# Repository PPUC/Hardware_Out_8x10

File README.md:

# Lamp Matrix PCB for PPUC Project
This is the hardware for a LED lamp matrix card which was designed for the PPUC pinball project, but can be useful in other applications as well. The intentionally usecase is to connect an original equipped pinball playfield (including cable harness). Normally I'd prefer a serial WS2812 LED strip to do a DIY pinball but if all the LEDs and cables are in place already, it is useful to connect the lamp matrix directly (for LED use only, not for incandescent bulbs as power of the outputs is limited).
It is designed for being low cost and functional for experimental use.  
Not everything is tested nor does it fulfill EMC or any other specifications.  
Use at your own risk!
To make use of anything of this project a basic understanding of electronics and programming is necessary. Nothing of it is "plug and play". I'm surely not liable for any damage to assemblies, pinball machines or even persons.

## Picture of the Board

## Name
Out_8x10 as it has 18 outputs. 8 high side switches and 10 low side switches which can form a 8x10 matrix but could also be used as simple high side and low side outputs.  

## Power Supply
The IO card must be supplied by 5 V (+-0.5 V) for logic and nominal 20 V for outputs. As these outputs are open source and open drain, the 20 V supply can actually be 7 V up to 26 V. In the circuit diagram the voltage is called 20 V.

## Controller
A RP2040 is used for it's cost/performance ratio. It is the same controller that is used in the Raspberry Pi Pico.

## Communication Interfaces
* RS_485: main communication interface for controlling the outputs. Usually connected to a host interface like a PC or Raspberry Pi or similar.
* USB C: for programming, debug and flashing
* Serial Wire: alternative for programming, debug and flashing

## Switches (on board)
* Reset: hardware reset for controller (RP2040)
* Boot: if active, the board connects to a PC like an USB stick. Usually used for programming the code into the flash memory on the board.
* DIP-switches: usually used to select an address for RS485 (16 combinations)

## High Side Switch Outputs
There are 8 outputs featuring a high side switch, usually used for lamp coloums. The voltage is derived form 20 V power connection. Current and power is limited by a linear regulator (78L24) wich is actually not used for regulating the voltage but to protect the switch form overload in case of a short circuit. Each output can drive a constant current of 100 mA witch is normaly sufficiant for 10 LED lamps (e.g. 10 rows of LEDs). Short term peak current is about 300 mA. The 20 V supply can actually range from 7 V to 26 V (the lower limit is derived from UGS of the high side FET).

## Low Side Switch Outputs
There are 10 outputs featuring a low side switch, usually used for lamp rows. The outputs are open drain and drive currents up to 3 A with a load connected to a voltage of up to 30 V.

## Special Output
One special output is available for high speed signals. The voltage is 5 V, it is a push pull output that can drive a current up to 8 mA. It can be used to e.g. control a WS2812 LED strip.

## Connectors
There are pads for connectors that fit S.A.M. systems and also WPC systems. Be aware that J5 (WPC columns) is actually not in the PCB layout as it can be mounted on pins 1 to 9 of J6 (S.A.M. columns). The pinning is unfortunately vice versa so the connector of the original WPC cable harness has to be rotated by 180° (cables go to the inner side of PCB).

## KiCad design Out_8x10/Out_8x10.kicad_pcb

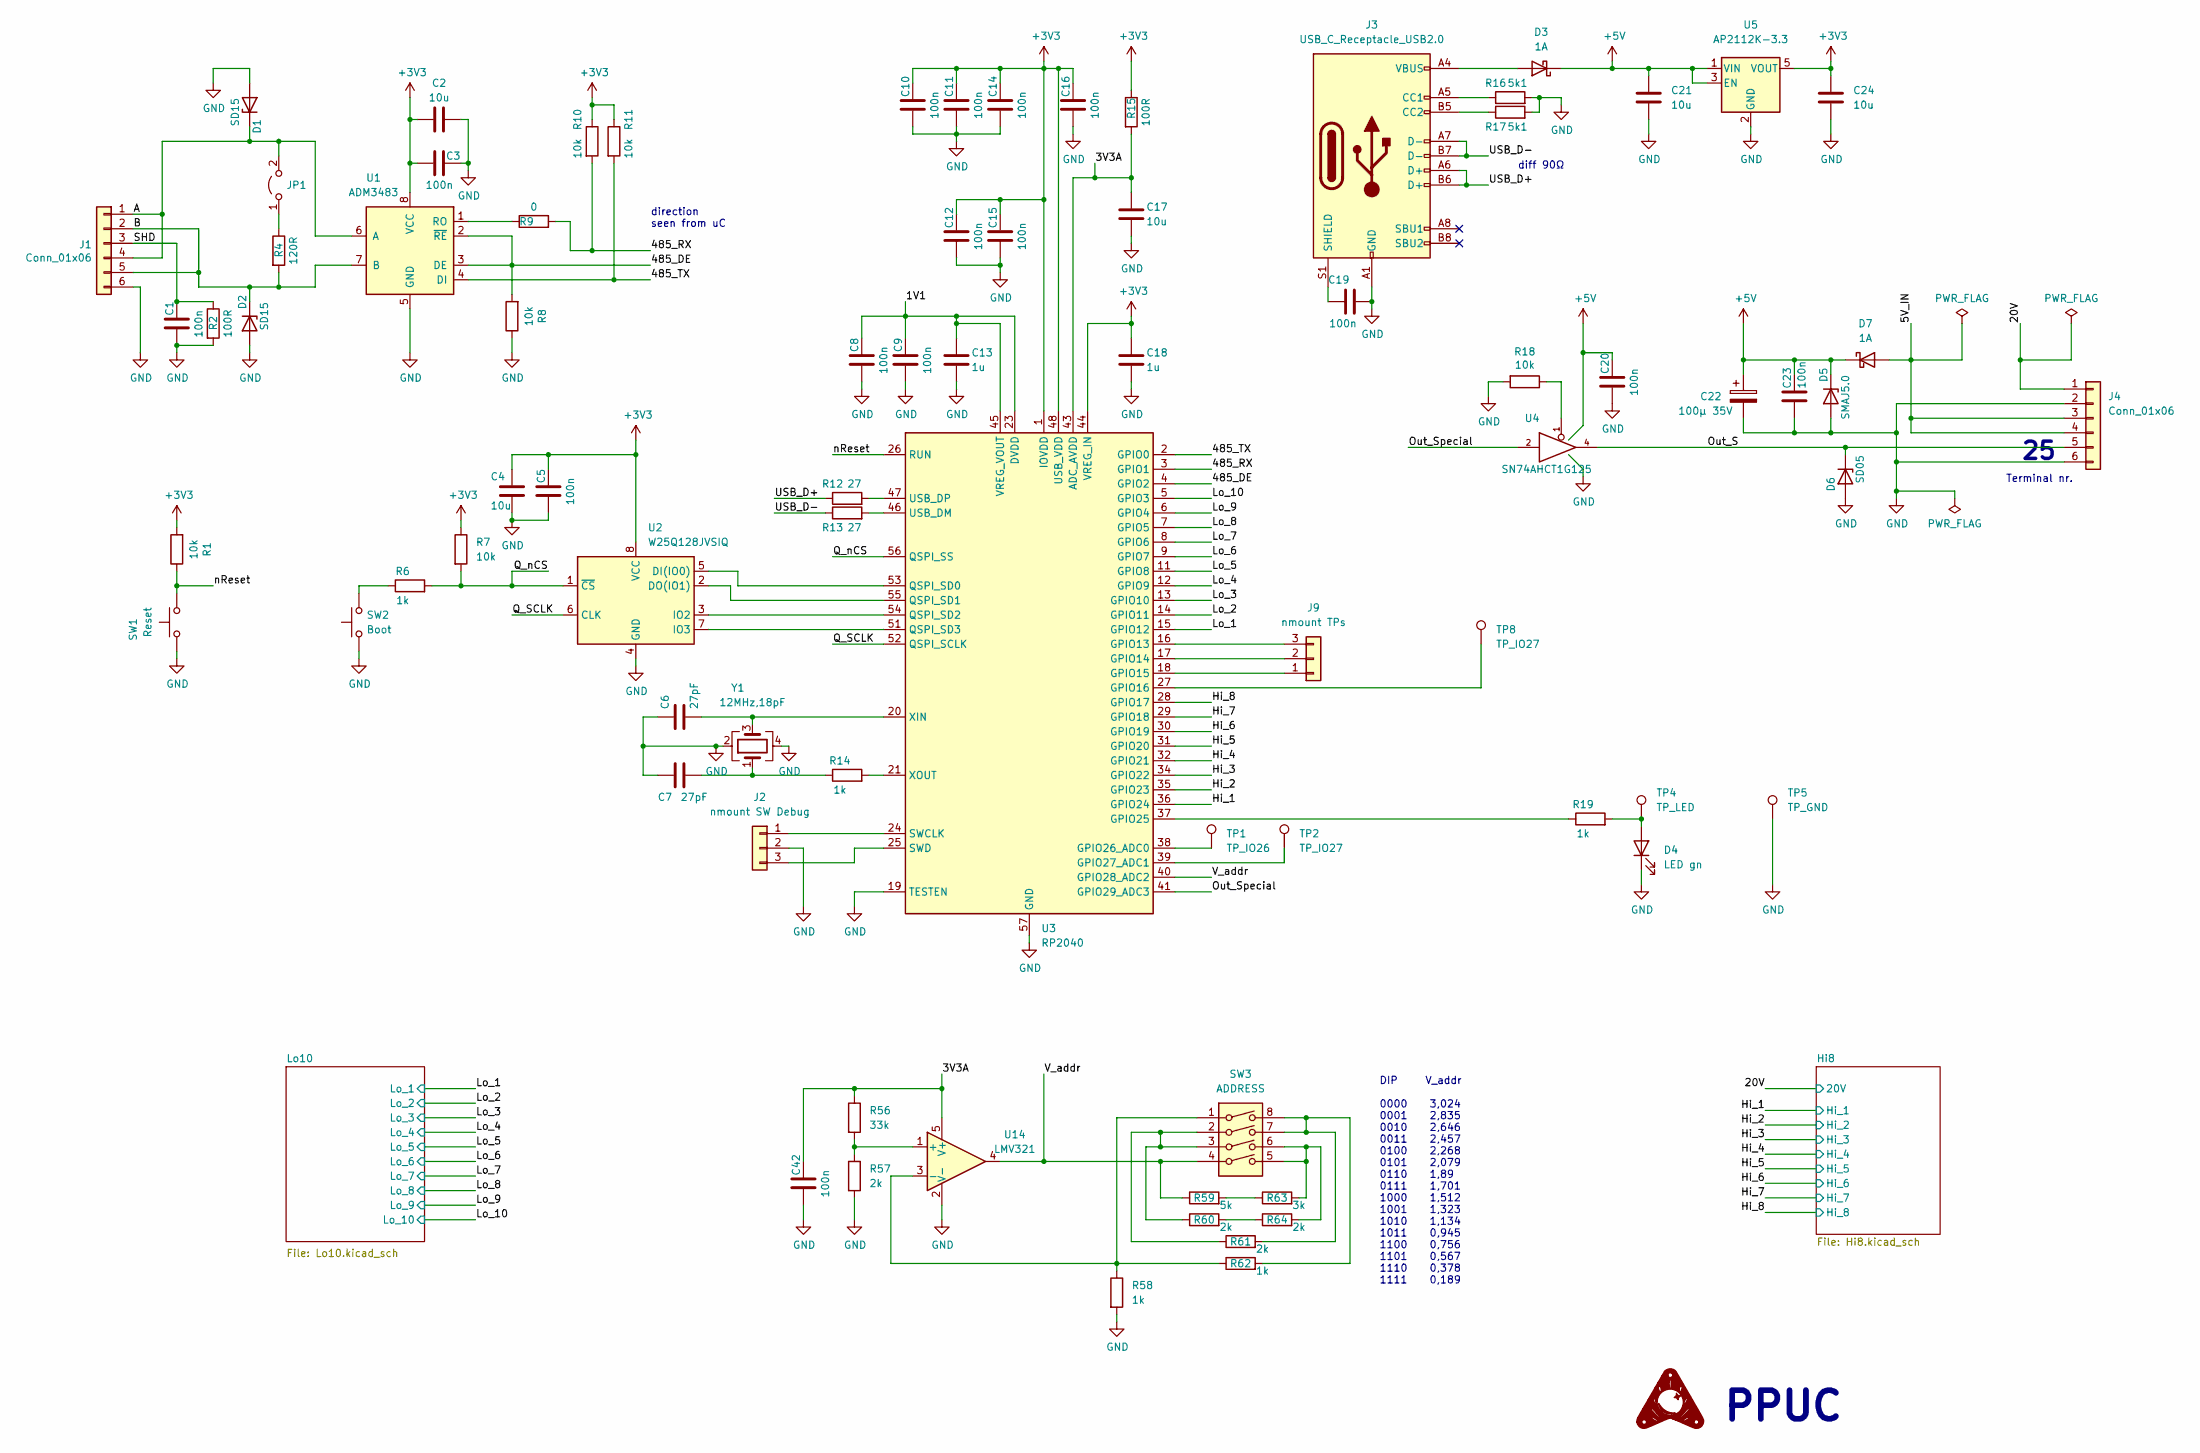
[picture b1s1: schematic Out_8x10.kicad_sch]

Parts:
C1, C3, C5, C8, C9, C10, C11, C12, C14, C15, C16, C19, C20, C23, C42: 100n; C_0402_1005Metric
C2, C4, C17, C21, C24: 10u; C_0603_1608Metric
C6, C7: 27pF; C_0402_1005Metric
C13, C18: 1u; C_0402_1005Metric
C22: 100µ 35V; CP_Elec_6.3x7.7; JLCPCB Rotation Offset 180
D1, D2: SD15; D_SOD-323
D3, D7: 1A; D_SOD-323
D4: LED gn; LED_0805_2012Metric
D5: SMAJ5.0; D_SMA
D6: SD05; D_SOD-323
J1, J4: Conn_01x06; Terminal_Block_RTMPin
J2: nmount SW Debug; PinSocket_1x03_P2.54mm_Vertical
J3: USB_C_Receptacle_USB2.0; USB_C_Receptacle_XKB_U262-16XN-4BVC11
J9: nmount TPs; PinSocket_1x03_P2.54mm_Vertical
JP1: Jumper_2_Open; PinHeader_1x02_P2.54mm_Vertical
R1, R7, R8, R10, R11, R18: 10k; R_0603_1608Metric
R2, R15: 100R; R_0603_1608Metric
R4: 120R; R_0603_1608Metric
R6, R14, R19, R58, R62: 1k; R_0402_1005Metric
R9: 0; R_0603_1608Metric
R12, R13: 27; R_0402_1005Metric
R16, R17: 5k1; R_0603_1608Metric
R56: 33k; R_0603_1608Metric
R57, R60, R61, R64: 2k; R_0603_1608Metric
R59: 5k; R_0603_1608Metric
R63: 3k; R_0603_1608Metric
SW1: Reset; SW_SPST_SKQG_WithStem
SW2: Boot; SW_SPST_SKQG_WithStem
SW3: ADDRESS; SW_DIP_SPSTx04_Slide_6.7x11.72mm_W8.61mm_P2.54mm_LowProfile; JLCPCB Rotation Offset 90
TP1: TP_IO26; TestPoint_Pad_D1.0mm
TP2, TP8: TP_IO27; TestPoint_Pad_D1.0mm
TP4: TP_LED; Pin_D1.0mm_L10.0mm
TP5: TP_GND; Pin_D1.0mm_L10.0mm
U1: ADM3483; SOIC-8_3.9x4.9mm_P1.27mm
U2: W25Q128JVSIQ; SOIC-8_5.23x5.23mm_P1.27mm
U3: RP2040; QFN-56-1EP_7x7mm_P0.4mm_EP3.2x3.2mm; JLCPCB Rotation Offset -90
U4: SN74AHCT1G125; SOT-23-5
U5: AP2112K-3.3; SOT-23-5; JLCPCB Rotation Offset 90
U14: LMV321; SOT-23-5
Y1: 12MHz,18pF; Crystal_SMD_3225-4Pin_3.2x2.5mm

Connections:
+3V3: C2.1, C3.1, C4.1, C5.1, C10.1, C11.1, C12.1, C14.1, C15.1, C16.1, C18.1, C24.1, R1.2, R7.1, R10.1, R11.1, R15.1, U1.8 (VCC), U2.8 (VCC), U3.1 (IOVDD), U3.10 (IOVDD), U3.22 (IOVDD), U3.33 (IOVDD), U3.42 (IOVDD), U3.44 (VREG_IN), U3.48 (USB_VDD), U3.49 (IOVDD), U5.5 (VOUT)
+5V: C20.1, C21.1, C22.1, C23.1, D3.1 (K), D5.1 (K), D7.1 (K), U4.5 (VCC), U5.1 (VIN), U5.3 (EN)
/1V1: C8.1, C9.1, C13.1, U3.23 (DVDD), U3.45 (VREG_VOUT), U3.50 (DVDD)
/3V3A: C17.1, C42.1, R15.2, R56.1, U3.43 (ADC_AVDD), U14.5 (V+)
/485_DE: R8.2, U1.2 (~RE), U1.3 (DE), U3.4 (GPIO2)
/485_RX: R9.2, R10.2, U3.3 (GPIO1)
/485_TX: R11.2, U1.4 (DI), U3.2 (GPIO0)
/A: D1.1 (K), J1.1, J1.4, JP1.2 (B), U1.6 (A)
/B: D2.1 (K), J1.2, J1.5, R4.2, U1.7 (B)
/Hi_1: U3.36 (GPIO24); also elsewhere on the board
/Hi_2: U3.35 (GPIO23); also elsewhere on the board
/Hi_3: U3.34 (GPIO22); also elsewhere on the board
/Hi_4: U3.32 (GPIO21); also elsewhere on the board
/Hi_5: U3.31 (GPIO20); also elsewhere on the board
/Hi_6: U3.30 (GPIO19); also elsewhere on the board
/Hi_7: U3.29 (GPIO18); also elsewhere on the board
/Hi_8: U3.28 (GPIO17); also elsewhere on the board
/Lo_1: U3.15 (GPIO12); also elsewhere on the board
/Lo_2: U3.14 (GPIO11); also elsewhere on the board
/Lo_3: U3.13 (GPIO10); also elsewhere on the board
/Lo_4: U3.12 (GPIO9); also elsewhere on the board
/Lo_5: U3.11 (GPIO8); also elsewhere on the board
/Lo_6: U3.9 (GPIO7); also elsewhere on the board
/Lo_7: U3.8 (GPIO6); also elsewhere on the board
/Lo_8: U3.7 (GPIO5); also elsewhere on the board
/Lo_9: U3.6 (GPIO4); also elsewhere on the board
/Lo_10: U3.5 (GPIO3); also elsewhere on the board
/Out_S: D6.1 (K), J4.5, U4.4
/Out_Special: U3.41 (GPIO29_ADC3), U4.2
/Q_SCLK: U2.6 (CLK), U3.52 (QSPI_SCLK)
/Q_nCS: R6.2, R7.2, U2.1 (~CS), U3.56 (QSPI_SS)
/SHD: C1.1, J1.3, R2.1
/USB_D+: J3.A6 (D+), J3.B6 (D+), R12.1
/USB_D-: J3.A7 (D-), J3.B7 (D-), R13.1
/V_addr: R59.1, SW3.4, U3.40 (GPIO28_ADC2), U14.4
/nReset: R1.1, SW1.2, U3.26 (RUN)
unnamed: C6.2, U3.20 (XIN), Y1.3
unnamed: C7.2, R14.1, Y1.1
unnamed: C19.1, J3.S1 (SHIELD)
unnamed: D3.2 (A), J3.A4 (VBUS), J3.A9 (VBUS), J3.B4 (VBUS), J3.B9 (VBUS)
unnamed: D4.2 (A), R19.2, TP4.1
unnamed: J2.1, U3.24 (SWCLK)
unnamed: J2.3, U3.25 (SWD)
unnamed: J3.A5 (CC1), R16.1
unnamed: J3.B5 (CC2), R17.1
unnamed: J9.1, U3.18 (GPIO15)
unnamed: J9.2, U3.17 (GPIO14)
unnamed: J9.3, U3.16 (GPIO13)
unnamed: JP1.1 (A), R4.1
unnamed: R6.1, SW2.2
unnamed: R9.1, U1.1 (RO)
unnamed: R12.2, U3.47 (USB_DP)
unnamed: R13.2, U3.46 (USB_DM)
unnamed: R14.2, U3.21 (XOUT)
unnamed: R18.1, U4.1
unnamed: R19.1, U3.37 (GPIO25)
unnamed: R56.2, R57.1, U14.1 (+)
unnamed: R58.1, R62.1, SW3.1, U14.3 (-)
unnamed: R59.2, R63.1
unnamed: R60.1, R61.1, SW3.2, SW3.3
unnamed: R60.2, R64.1
unnamed: R61.2, R62.2, SW3.7, SW3.8
unnamed: R63.2, R64.2, SW3.5, SW3.6
unnamed: TP1.1, U3.38 (GPIO26_ADC0)
unnamed: TP2.1, U3.39 (GPIO27_ADC1)
unnamed: TP8.1, U3.27 (GPIO16)
unnamed: U2.2 (DO(IO1)), U3.55 (QSPI_SD1)
unnamed: U2.3 (IO2), U3.54 (QSPI_SD2)
unnamed: U2.5 (DI(IO0)), U3.53 (QSPI_SD0)
unnamed: U2.7 (IO3), U3.51 (QSPI_SD3)

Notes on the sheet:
DIP V_addr 0000 3,024 0001 2,835 0010 2,646 0011 2,457 0100 2,268 0101 2,079 0110 1,89 0111 1,701 1000 1,512 1001 1,323 1010 1,134 1011 0,945 1100 0,756 1101 0,567 1110 0,378 1111 0,189
diff 90Ω
Terminal nr.
direction seen from uC
PPUC

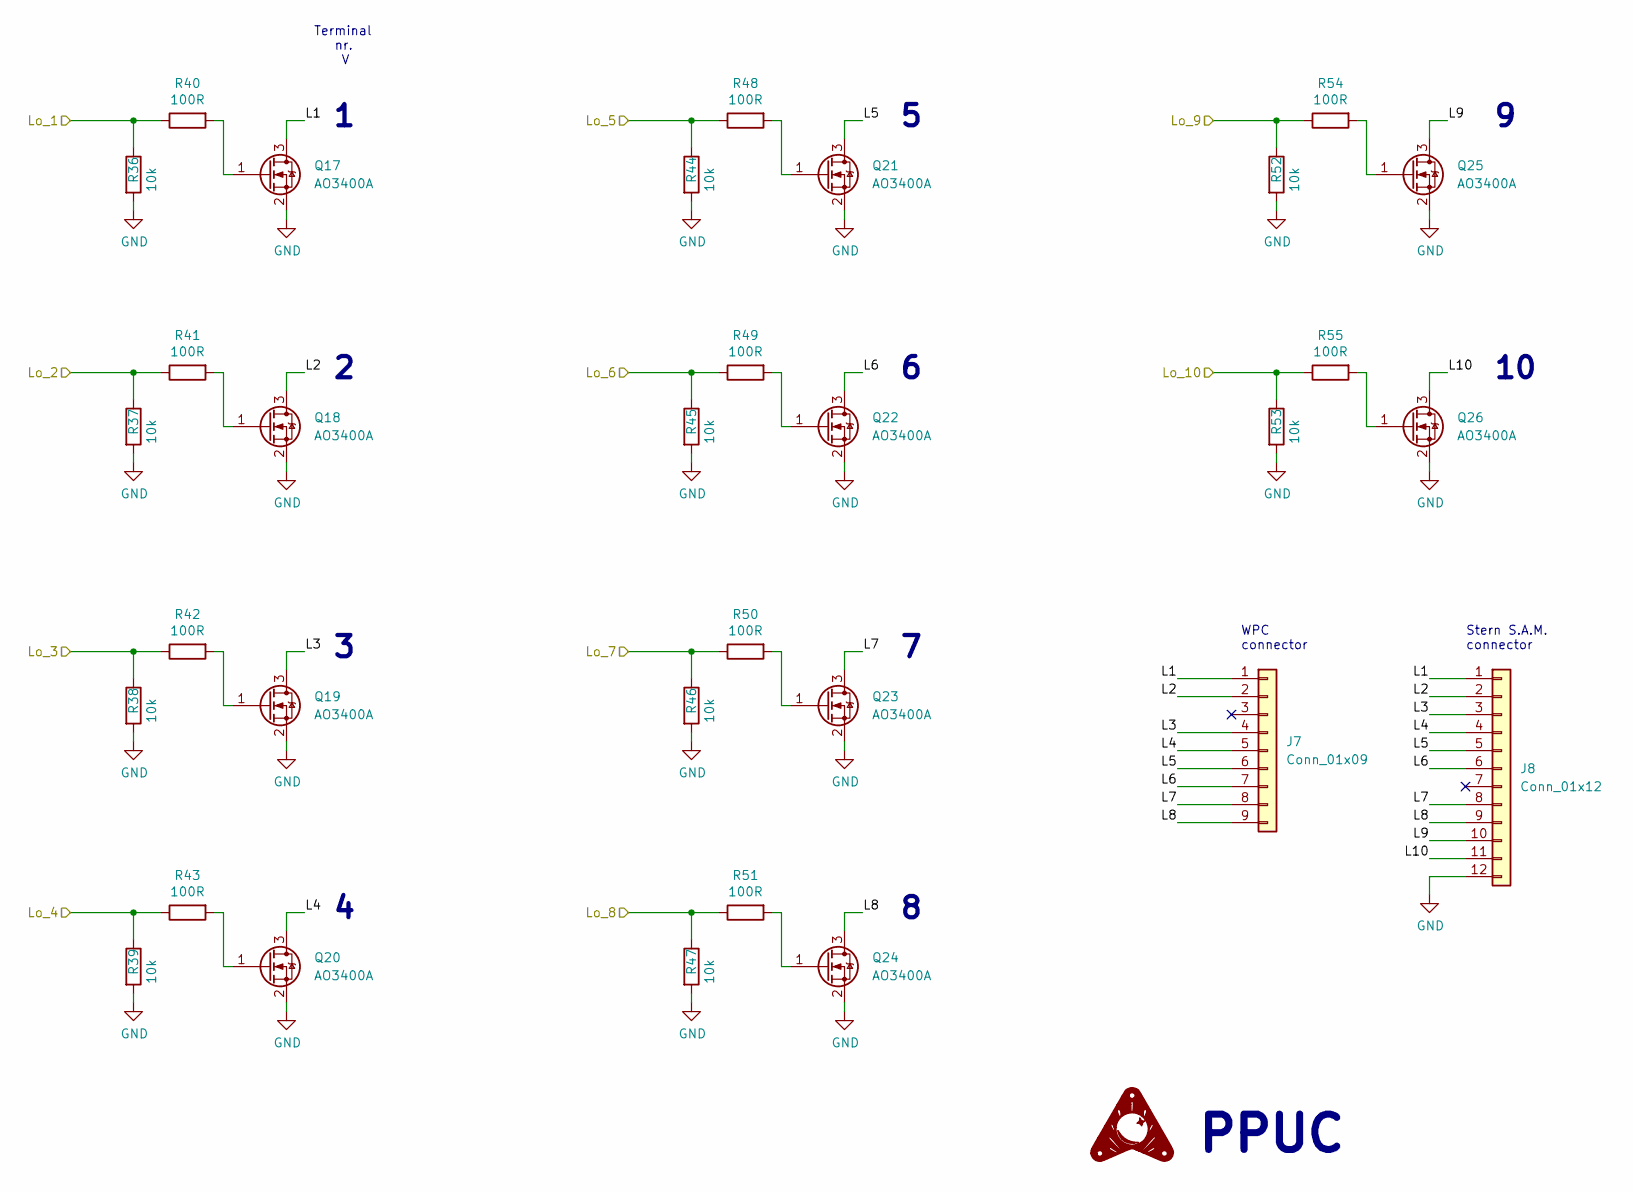
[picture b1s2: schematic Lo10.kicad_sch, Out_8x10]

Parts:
J7: Conn_01x09; Molex_KK-254_AE-6410-09A_1x09_P2.54mm_Vertical
J8: Conn_01x12; Molex_KK-396_5273-12A_1x12_P3.96mm_Vertical
Q17, Q18, Q19, Q20, Q21, Q22, Q23, Q24, Q25, Q26: AO3400A; SOT-23
R36, R37, R38, R39, R44, R45, R46, R47, R52, R53: 10k; R_0603_1608Metric
R40, R41, R42, R43, R48, R49, R50, R51, R54, R55: 100R; R_0603_1608Metric

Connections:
/Lo10/L1: J7.1, J8.1, Q17.3 (D)
/Lo10/L2: J7.2, J8.2, Q18.3 (D)
/Lo10/L3: J7.4, J8.3, Q19.3 (D)
/Lo10/L4: J7.5, J8.4, Q20.3 (D)
/Lo10/L5: J7.6, J8.5, Q21.3 (D)
/Lo10/L6: J7.7, J8.6, Q22.3 (D)
/Lo10/L7: J7.8, J8.8, Q23.3 (D)
/Lo10/L8: J7.9, J8.9, Q24.3 (D)
/Lo10/L9: J8.10, Q25.3 (D)
/Lo10/L10: J8.11, Q26.3 (D)
/Lo_1: R36.1, R40.1; also elsewhere on the board
/Lo_2: R37.1, R41.1; also elsewhere on the board
/Lo_3: R38.1, R42.1; also elsewhere on the board
/Lo_4: R39.1, R43.1; also elsewhere on the board
/Lo_5: R44.1, R48.1; also elsewhere on the board
/Lo_6: R45.1, R49.1; also elsewhere on the board
/Lo_7: R46.1, R50.1; also elsewhere on the board
/Lo_8: R47.1, R51.1; also elsewhere on the board
/Lo_9: R52.1, R54.1; also elsewhere on the board
/Lo_10: R53.1, R55.1; also elsewhere on the board
unnamed: Q17.1 (G), R40.2
unnamed: Q18.1 (G), R41.2
unnamed: Q19.1 (G), R42.2
unnamed: Q20.1 (G), R43.2
unnamed: Q21.1 (G), R48.2
unnamed: Q22.1 (G), R49.2
unnamed: Q23.1 (G), R50.2
unnamed: Q24.1 (G), R51.2
unnamed: Q25.1 (G), R54.2
unnamed: Q26.1 (G), R55.2

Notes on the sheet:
PPUC
WPC connector
Terminal nr. V
Stern S.A.M. connector

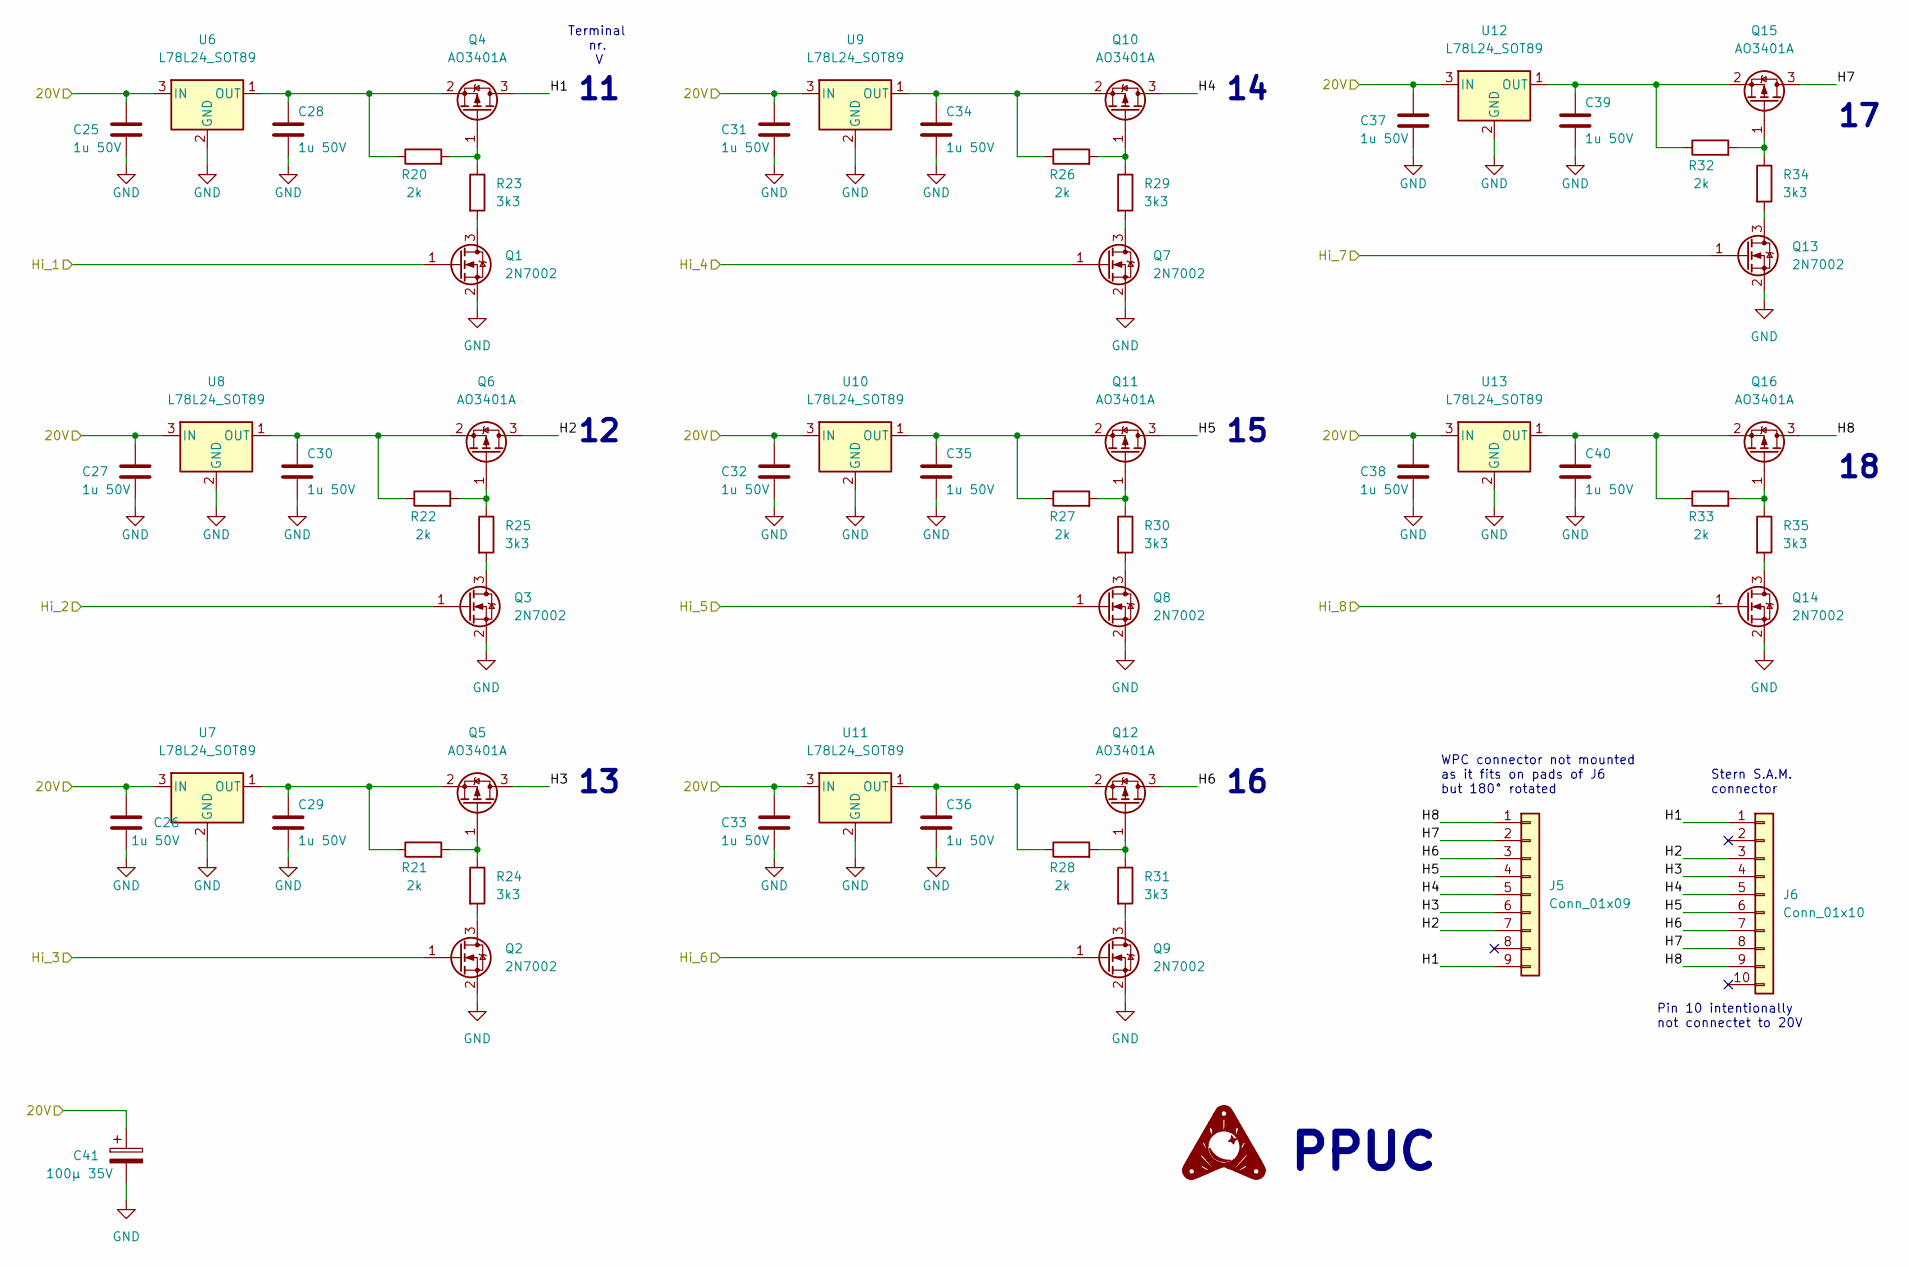
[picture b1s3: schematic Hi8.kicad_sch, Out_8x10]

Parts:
C25, C26, C27, C28, C29, C30, C31, C32, C33, C34, C35, C36, C37, C38, C39, C40: 1u 50V; C_0603_1608Metric
C41: 100µ 35V; CP_Elec_6.3x7.7; JLCPCB Rotation Offset 180
J5: Conn_01x09; Molex_KK-396_5273-09A_1x09_P3.96mm_Vertical
J6: Conn_01x10; Molex_KK-396_5273-10A_1x10_P3.96mm_Vertical
Q1, Q2, Q3, Q7, Q8, Q9, Q13, Q14: 2N7002; SOT-23
Q4, Q5, Q6, Q10, Q11, Q12, Q15, Q16: AO3401A; SOT-23
R20, R21, R22, R26, R27, R28, R32, R33: 2k; R_0603_1608Metric
R23, R24, R25, R29, R30, R31, R34, R35: 3k3; R_0603_1608Metric
U6, U7, U8, U9, U10, U11, U12, U13: L78L24_SOT89; SOT-89-3

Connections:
/Hi8/H1: J5.9, J6.1, Q4.3 (D)
/Hi8/H2: J5.7, J6.3, Q6.3 (D)
/Hi8/H3: J5.6, J6.4, Q5.3 (D)
/Hi8/H4: J5.5, J6.5, Q10.3 (D)
/Hi8/H5: J5.4, J6.6, Q11.3 (D)
/Hi8/H6: J5.3, J6.7, Q12.3 (D)
/Hi8/H7: J5.2, J6.8, Q15.3 (D)
/Hi8/H8: J5.1, J6.9, Q16.3 (D)
/Hi_1: Q1.1 (G); also elsewhere on the board
/Hi_2: Q3.1 (G); also elsewhere on the board
/Hi_3: Q2.1 (G); also elsewhere on the board
/Hi_4: Q7.1 (G); also elsewhere on the board
/Hi_5: Q8.1 (G); also elsewhere on the board
/Hi_6: Q9.1 (G); also elsewhere on the board
/Hi_7: Q13.1 (G); also elsewhere on the board
/Hi_8: Q14.1 (G); also elsewhere on the board
unnamed: C28.1, Q4.2 (S), R20.1, U6.1 (OUT)
unnamed: C29.1, Q5.2 (S), R21.1, U7.1 (OUT)
unnamed: C30.1, Q6.2 (S), R22.1, U8.1 (OUT)
unnamed: C34.1, Q10.2 (S), R26.1, U9.1 (OUT)
unnamed: C35.1, Q11.2 (S), R27.1, U10.1 (OUT)
unnamed: C36.1, Q12.2 (S), R28.1, U11.1 (OUT)
unnamed: C39.1, Q15.2 (S), R32.1, U12.1 (OUT)
unnamed: C40.1, Q16.2 (S), R33.1, U13.1 (OUT)
unnamed: Q1.3 (D), R23.2
unnamed: Q2.3 (D), R24.2
unnamed: Q3.3 (D), R25.2
unnamed: Q4.1 (G), R20.2, R23.1
unnamed: Q5.1 (G), R21.2, R24.1
unnamed: Q6.1 (G), R22.2, R25.1
unnamed: Q7.3 (D), R29.2
unnamed: Q8.3 (D), R30.2
unnamed: Q9.3 (D), R31.2
unnamed: Q10.1 (G), R26.2, R29.1
unnamed: Q11.1 (G), R27.2, R30.1
unnamed: Q12.1 (G), R28.2, R31.1
unnamed: Q13.3 (D), R34.2
unnamed: Q14.3 (D), R35.2
unnamed: Q15.1 (G), R32.2, R34.1
unnamed: Q16.1 (G), R33.2, R35.1

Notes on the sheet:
PPUC
Terminal nr. V
Stern S.A.M. connector
Pin 10 intentionally not connectet to 20V
WPC connector not mounted as it fits on pads of J6 but 180° rotated

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
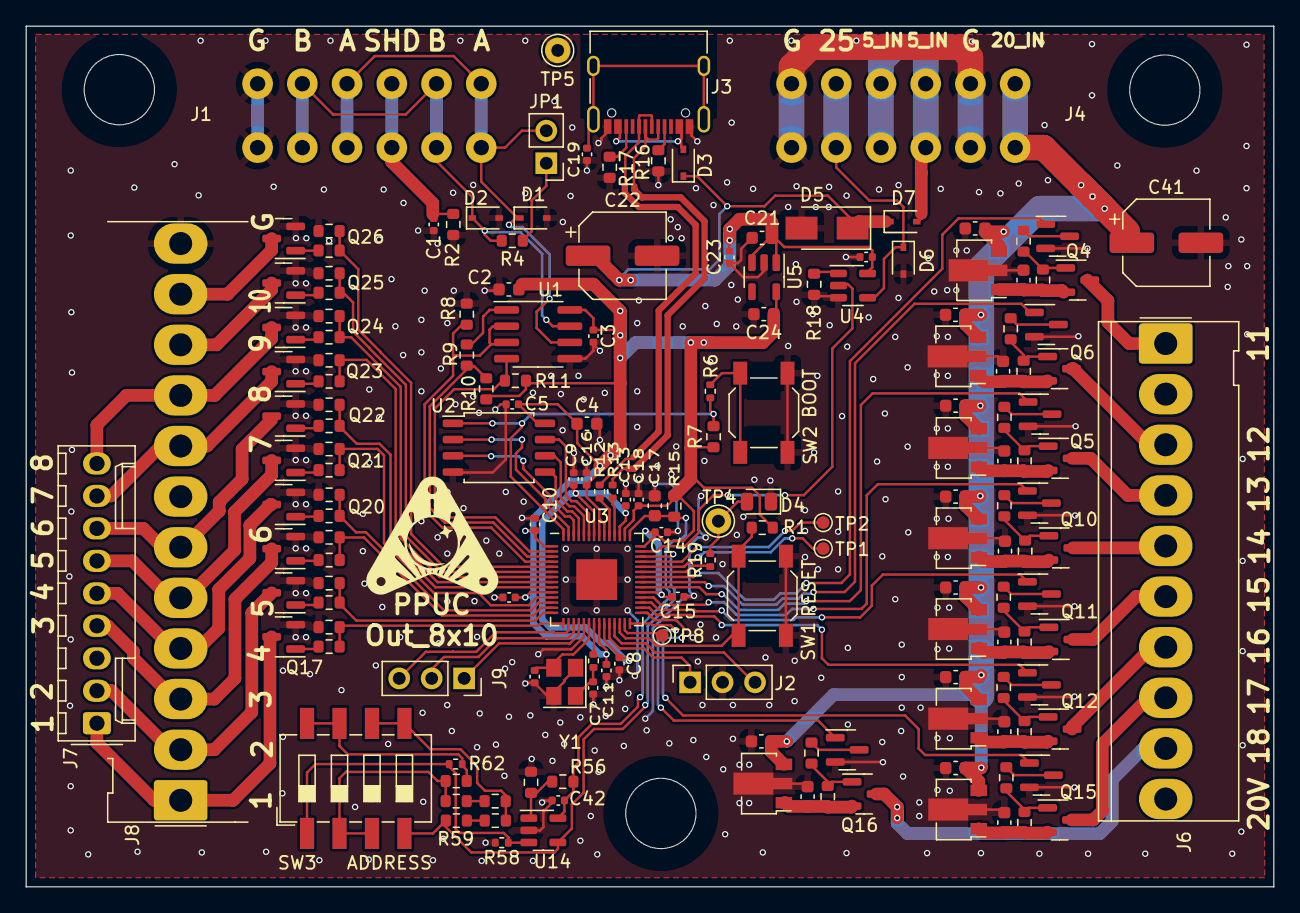
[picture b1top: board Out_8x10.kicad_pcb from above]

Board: 2 copper layers, 97.6 x 67.3 mm, 169 parts (0 on the bottom side), 125 nets.

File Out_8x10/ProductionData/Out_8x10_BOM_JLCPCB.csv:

Comment,Designator,Footprint,LCSC
"100n","C1,C3,C5,C8,C9,C10,C11,C12,C14,C15,C16,C19,C20,C23,C42","Capacitor_SMD:C_0402_1005Metric","C1525"
"1u","C13,C18","Capacitor_SMD:C_0402_1005Metric","C52923"
"10u","C2,C4,C17,C21,C24","Capacitor_SMD:C_0603_1608Metric","C19702"
"100µ 35V","C22,C41","Capacitor_SMD:CP_Elec_6.3x7.7","C2836437"
"1u 50V","C25,C26,C27,C28,C29,C30,C31,C32,C33,C34,C35,C36,C37,C38,C39,C40","Capacitor_SMD:C_0603_1608Metric","C15849"
"27pF","C6,C7","Capacitor_SMD:C_0402_1005Metric","C1557"
"SD15","D1,D2","Diode_SMD:D_SOD-323","C502529"
"1A","D3","Diode_SMD:D_SOD-323","C191023"
"LED gn","D4","LED_SMD:LED_0805_2012Metric","C2297"
"SMAJ5.0","D5","Diode_SMD:D_SMA","C2925443"
"SD05","D6","Diode_SMD:D_SOD-323","C2972756"
"T500mA,<0.3Ω","F1","Fuse:Fuse_1206_3216Metric","C206993"
"USB_C_Receptacle_USB2.0","J3","Connector_USB:USB_C_Receptacle_XKB_U262-16XN-4BVC11","C709357"
"2N7002","Q1,Q2,Q3,Q7,Q8,Q9,Q13,Q14","Package_TO_SOT_SMD:SOT-23","C8545"
"AO3400A","Q17,Q18,Q19,Q20,Q21,Q22,Q23,Q24,Q25,Q26","Package_TO_SOT_SMD:SOT-23","C20917"
"AO3401A","Q4,Q5,Q6,Q10,Q11,Q12,Q15,Q16","Package_TO_SOT_SMD:SOT-23","C15127"
"10k","R1,R7,R8,R10,R11,R18,R36,R37,R38,R39,R44,R45,R46,R47,R52,R53","Resistor_SMD:R_0603_1608Metric","C25804"
"27","R12,R13","Resistor_SMD:R_0402_1005Metric","C138021"
"5k1","R16,R17","Resistor_SMD:R_0603_1608Metric","C23186"
"100R","R2,R15,R40,R41,R42,R43,R48,R49,R50,R51,R54,R55","Resistor_SMD:R_0603_1608Metric","C22775"
"3k3","R23,R24,R25,R29,R30,R31,R34,R35","Resistor_SMD:R_0603_1608Metric","C22978"
"1k","R3,R5,R6,R14,R19,R58,R62","Resistor_SMD:R_0402_1005Metric","C11702"
"120R","R4","Resistor_SMD:R_0603_1608Metric","C22787"
"33k","R56","Resistor_SMD:R_0603_1608Metric","C4216"
"2k","R20,R21,R22,R26,R27,R28,R32,R33,R57,R60,R61,R64","Resistor_SMD:R_0603_1608Metric","C22975"
"5k","R59","Resistor_SMD:R_0603_1608Metric","C101077"
"3k","R63","Resistor_SMD:R_0603_1608Metric","C4211"
"0","R9","Resistor_SMD:R_0603_1608Metric","C21189"
"Reset","SW1","Button_Switch_SMD:SW_SPST_SKQG_WithStem","C318884"
"Boot","SW2","Button_Switch_SMD:SW_SPST_SKQG_WithStem","C318884"
"ADDRESS","SW3","Button_Switch_SMD:SW_DIP_SPSTx04_Slide_6.7x11.72mm_W8.61mm_P2.54mm_LowProfile","C54950"
"ADM3483","U1","Package_SO:SOIC-8_3.9x4.9mm_P1.27mm","C609792"
"LMV321","U14","Package_TO_SOT_SMD:SOT-23-5","C7972"
"W25Q128JVSIQ","U2","Package_SO:SOIC-8_5.23x5.23mm_P1.27mm","C97521"
"RP2040","U3","Package_DFN_QFN:QFN-56-1EP_7x7mm_P0.4mm_EP3.2x3.2mm","C2040"
"SN74AHCT1G125","U4","Package_TO_SOT_SMD:SOT-23-5","C7484"
"AP2112K-3.3","U5","Package_TO_SOT_SMD:SOT-23-5","C51118"
"L78L24_SOT89","U6,U7,U8,U9,U10,U11,U12,U13","Package_TO_SOT_SMD:SOT-89-3","C5309539"
"12MHz,18pF","Y1","Crystal:Crystal_SMD_3225-4Pin_3.2x2.5mm","C9002"

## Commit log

2023-10-10 initial
2023-10-11 updated layout
2023-10-20 Analog DIP
2023-10-20 schmaPDF updated
2023-10-22 TPs to RM2.54
2023-11-03 added picture
2024-03-27 prod. data
2024-12-01 V1.0.0
